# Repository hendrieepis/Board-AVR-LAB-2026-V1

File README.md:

# 📋 Panduan Desain: Shield Arduino Mega 2560 — PENS Expansion Board V2.0

---

## 📐 Spesifikasi Teknis

### 1. Dimensi & Form Factor

| Parameter | Nilai |
|---|---|
| Panjang | 101.6 mm / 4000 mil (exact Arduino Mega R3) |
| Lebar | 53.3 mm / 2098 mil (exact Arduino Mega R3) |
| Ketebalan PCB | 1.6 mm / 63 mil (FR4) |
| Lubang mounting | 4× (diameter 3.2 mm / 126 mil) |
| Jumlah layer | 2 (dua layer) |
| Konektor ke Mega | *Stackable female header* 2.54 mm / 100 mil |

### 2. Sumber Daya

- **Source:** Arduino Mega 5V rail saja (tidak ada *external power*)
- **Decoupling:** 4× 100 nF (0805) — distribusi dekat cluster MOSFET untuk menjaga stabilitas switching

### 3. Pin Assignment (WAJIB SAMA DENGAN WOKWI)

> ⚠️ **PENTING:** Pin *assignment* harus persis sama dengan simulator Wokwi PENS Elka. Jangan merubah *mapping* pin karena akan menyebabkan kode tidak kompatibel antara simulator dan *hardware* fisik.

#### 3.1. LED Array (8 LED Merah — PORTA)

| Arduino Pin | AVR Port | Device | Warna | Reference |
|---|---|---|---|---|
| D22 | PA0 | LED1 | Merah | D0 |
| D23 | PA1 | LED8 | Merah | D1 |
| D24 | PA2 | LED7 | Merah | D2 |
| D25 | PA3 | LED5 | Merah | D3 |
| D26 | PA4 | LED3 | Merah | D4 |
| D27 | PA5 | LED6 | Merah | D5 |
| D28 | PA6 | LED4 | Merah | D6 |
| D29 | PA7 | LED2 | Merah | D7 |

**Package:** LED SMD 0805 (`LED_SMD:LED_0805_2012Metric_Pad1.15x1.40mm_HandSolder`)

**Tata letak PCB:** Susun LED dalam satu baris dari PA0 di kiri hingga PA7 di kanan agar mahasiswa bisa membaca *pattern* `PORTA` secara visual.

#### 3.2. LED Indikator (2 LED)

| Arduino Pin | AVR Port | Device | Warna | Reference |
|---|---|---|---|---|
| D12 | PB6 | LED9 | Merah | DA1 |
| D13 | PB7 | LED10 | Hijau | DB1 |

**Package:** LED SMD 0805 (sama dengan LED array)

#### 3.3. Buzzer

| Arduino Pin | AVR Port | Device | Reference |
|---|---|---|---|
| D11 | PB5 | Buzzer (piezo/magnetic 5V) | BZ1 |

**Skema rangkaian:**

```
        +5V
         │
       ┌─┴─┐
     1 │ + │ BZ1
       │   │ Buzzer
     2 │   │
       └─┬─┘
         │
       ┌─┴─┐
       │R6 │ 1K
       └─┬─┘
         │ 3
   D11 1 ┤├─┐
    ●────┤  │ Q2
    │    ┤├─┘ BSS138
  ┌─┴─┐    │ 2
  │R5 │    │
  │1M │    │
  └─┬─┘    │
    │      │
   GND    GND
```

#### 3.4. Push Button (Active-LOW, 4 unit)

| Arduino Pin | AVR Port | Device | Reference |
|---|---|---|---|
| D10 | PB4 | BTN1 | SW1 |
| D9 | PH6 | BTN2 | SW2 |
| D8 | PH5 | BTN3 | SW3 |
| D7 | PH4 | BTN4 | SW4 |

**Skema rangkaian (debounce):**

```
   +5V
    │
  ┌─┴─┐
  │R13│ 10K
  └─┬─┘
    ●──── D7
  ┌─┴─┐
  │R14│ 1K
  └─┬─┘
    ●─────────┐
   o│         │
   SW4       ─┴─ C4
   SW_Push   ─┬─ 0.1uF
   o│         │
    ●─────────┘
    │
   GND
```

- **Package:** Tactile switch 6×6 mm THT (`Button_Switch_THT:SW_PUSH_6mm`)
- **Tinggi actuator:** Rekomendasi 7.3H (ergonomis untuk jari, tidak mudah rusak)
- Tombol aktif saat ditekan (menghubungkan pin ke GND)
- Menggunakan internal pull-up AVR (`INPUT_PULLUP` di kode) — tidak perlu resistor pull-up eksternal
- **Alasan pilih THT (bukan SMD):** Untuk praktikum mahasiswa, THT jauh lebih robust terhadap tekanan berulang dan perlakuan kasar. Jalur PCB tidak mudah rusak karena kaki pin masuk ke PTH (plated through-hole), bukan hanya solder di permukaan.

#### 3.5. Potensiometer & LDR (Input Analog)

| Arduino Pin | ADC Channel | Device | Reference | Tipe |
|---|---|---|---|---|
| A0 | ADC0 | POT1 | RV1 | Trimpot 10K |
| A1 | ADC1 | POT2 | RV2 | Trimpot 10K |
| A2 | ADC2 | LDR | R14 | GL5528 (5mm) |

**Package:**

- **Trimpot:** `Potentiometer_THT:Potentiometer_Bourns_3386P_Vertical` (Bourns 3386P 10K)
- **LDR:** `OptoDevice:R_LDR_5.1x4.3mm_P3.4mm_Vertical` (GL5528, pitch 3.4mm)

**Konfigurasi:**

- **Trimpot (RV1, RV2):** Voltage divider standar — Pin 1 ke +5V, Pin 3 ke GND, wiper (Pin 2) ke ADC
- **LDR (R14):** Voltage divider dengan resistor partner 10K (R_LDR ke +5V, R_10K ke GND, tap ke ADC)

---

## 🔌 Rangkaian Driver (MOSFET Isolation)

### Skema Driver LED (diulang untuk 8 LED PORTA + 2 LED indikator + Buzzer = 11 channel)

```
        +5V
         │
        ─┴─
        \ / D7
        ─┬─ LED
         │
       ┌─┴─┐
       │R32│ 1K
       └─┬─┘
         │ 3
  D29  1 ┤├─┐
   ●─────┤  │ Q12
   │     ┤├─┘ BSS138
 ┌─┴─┐     │ 2
 │R31│     │
 │1M │     │
 └─┬─┘     │
   │       │
  GND     GND
```

### Komponen per Channel LED

| # | Komponen | Nilai | Package | Fungsi |
|---|---|---|---|---|
| 1 | MOSFET | BSS138 | SOT-23 | Switch utama |
| 2 | Resistor pull-up | 10 kΩ | 0805 | Gate bias ke +5V |
| 3 | Resistor pull-down | 1 MΩ | 0805 | Cegah *flicker* saat pin INPUT |
| 4 | Resistor LED | 1 kΩ | 0805 | Pembatas arus LED (~3 mA) |
| 5 | LED | Merah/Hijau | 0805 | Indikator visual |

### Perilaku Driver

| Kondisi Pin Arduino | Gate MOSFET | LED |
|---|---|---|
| HIGH (5V) | HIGH | ON |
| LOW (0V) | LOW | OFF |
| INPUT (floating) | LOW (via R 1M) | OFF (tidak *flicker*) |

---

## 🔗 Antarmuka Komunikasi

### 1. Header I2C (JST PH 2.0, 4-pin)

**Reference:** J10 (atau salah satu dari J10, J11, J12)
**Footprint:** `Connector_JST:JST_PH_B4B-PH-K_1x04_P2.00mm_Vertical`

| Pin | Nama | Koneksi |
|---|---|---|
| 1 | GND | GND |
| 2 | VCC | +5V |
| 3 | SDA | Arduino pin 20 |
| 4 | SCL | Arduino pin 21 |

> **Catatan I2C pull-up:** ATmega2560 memiliki internal pull-up untuk SDA/SCL. Untuk modul I2C 5V standard (OLED, sensor), internal pull-up cukup. Jika menggunakan modul yang butuh pull-up eksternal, tambahkan resistor 4.7K di sisi modul.

### 2. Header SPI (JST PH 2.0, 6-pin)

**Reference:** J8 atau J9
**Footprint:** `Connector_JST:JST_PH_B6B-PH-K_1x06_P2.00mm_Vertical`

| Pin | Nama | Koneksi |
|---|---|---|
| 1 | GND | GND |
| 2 | VCC | +5V |
| 3 | MOSI | Arduino pin 51 |
| 4 | MISO | Arduino pin 50 |
| 5 | SCK | Arduino pin 52 |
| 6 | CS | Arduino pin 53 |

### 3. Header UART (JST PH 2.0, 4-pin)

**Reference:** J11 atau J12
**Footprint:** `Connector_JST:JST_PH_B4B-PH-K_1x04_P2.00mm_Vertical`

| Pin | Nama | Koneksi |
|---|---|---|
| 1 | GND | GND |
| 2 | VCC | +5V |
| 3 | TX1 | Arduino pin 18 (Serial1 TX) |
| 4 | RX1 | Arduino pin 19 (Serial1 RX) |

> Menggunakan **Serial1** (bukan Serial0) agar USB *debug* tetap tersedia untuk *Serial Monitor*.

**Praktik desain:**

- *Expose* semua pin yang digunakan di sisi atas dan bawah *board*
- *Silkscreen* dual label: "D22 / PA0", "A0 / ADC0", dst.
- Termasuk multiple *access point* untuk +5V dan GND

---

## 🎨 Prioritas Layout PCB

1. LED array disusun horizontal dari kiri ke kanan: PA0 → PA7
2. Push button dikelompokkan (4 tombol dalam satu baris)
3. Input analog dikelompokkan (2 trimpot + 1 LDR dalam satu area)
4. Connector JST di tepi *board* untuk akses kabel yang mudah
5. Silkscreen dual label (Arduino pin + AVR port) pada setiap pin *breakout*
6. Component reference (R1, C1, Q1, dll.) terlihat setelah *assembly*
7. **LDR penempatan:** Jauhkan minimal 20mm dari LED indikator untuk menghindari cross-talk cahaya

---

## 🏭 Spesifikasi PCB & Manufacturing

### Spesifikasi Fisik

| Parameter | Nilai |
|---|---|
| Layer | 2 |
| Material | FR4 1.6 mm |
| Copper weight | 1 oz (35 µm) |
| *Soldermask* | Hitam atau ungu |
| *Silkscreen* | Putih |
| Surface finish | HASL Lead-free (gratis) |
| *Ground plane* | *Bottom layer* |
| *Top layer* | Signal + komponen |

### Layer Strategy

```
TOP layer:    Body semua komponen (SMD & THT)
              SMD solder pads di sini
              Signal trace + VCC

BOTTOM layer: Solder pad untuk pin THT (saja)
              Ground plane solid
              Minimize signal trace
```

**Prinsip desain:**

- ❌ Bottom layer **JANGAN** dijadikan VCC plane
- ✅ Bottom layer = **Ground plane solid** (lebih baik untuk EMI, signal integrity, dan ADC accuracy)
- ✅ VCC sebagai **trace tebal** di top layer (0.5 mm / 20 mil)
- ✅ Decoupling capacitor (100 nF) dekat dengan cluster MOSFET
- ✅ Stitching via di area ground pour (1 via per 1–2 cm²) untuk low-impedance ground

### Bonus

**Bonus (optional, nilai plus):** Tambahkan **logo PENS** dan/atau **tulisan "Prodi Elka"** di area kosong **Bottom Silkscreen (B.Silkscreen)** sebagai identitas board. Bisa dalam bentuk:

- Logo PENS (import image ke KiCad)
- Tulisan "Prodi Elka - PENS" dengan KiCad text tool
- Atau kombinasi keduanya

Contoh:

```
┌────────────────────────────────────┐
│                                    │
│           [Logo PENS]              │
│                                    │
│        PENS EXPANSION BOARD        │
│           V2.0 (2026)              │
│      Prodi Teknik Elektronika      │
│                                    │
└────────────────────────────────────┘
```

---

## 📏 Design Rules untuk JLCPCB (Safe Settings)

> ⚠️ **PENTING:** Design rules di bawah ini adalah **recommended safe values** — lebih besar dari JLCPCB minimum — untuk margin terhadap manufacturing tolerance. Jangan mendesain persis di JLCPCB minimum karena risiko reject atau defect tinggi.

### Design Rules Cheatsheet

```
┌──────────────────────────────────────────────────────┐
│  PCB DESIGN RULES (JLCPCB Safe Settings)             │
├──────────────────────────────────────────────────────┤
│                                                      │
│  TRACK WIDTH:                                        │
│    Signal:  0.25 mm  (10 mil)                        │
│    Power:   0.5  mm  (20 mil)                        │
│                                                      │
│  CLEARANCE:                                          │
│    Track – track:  0.2 mm  (8 mil)                   │
│    Track – pad:    0.2 mm  (8 mil)                   │
│    Track – edge:   0.3 mm  (12 mil)                  │
│                                                      │
│  VIA:                                                │
│    Signal:  0.3 / 0.6 mm  (12 / 24 mil)              │
│    Power:   0.4 / 0.8 mm  (16 / 32 mil)              │
│                                                      │
│  HOLE (THT):                                         │
│    Min drill:     0.3 mm  (12 mil) – JLCPCB limit    │
│    Typical pin:   0.6 – 1.0 mm  (24 – 39 mil)        │
│    Annular ring:  0.15 mm  (6 mil) per side          │
│                                                      │
│  BOARD EDGE:                                         │
│    Copper – edge:     0.3 mm  (12 mil)               │
│    Component – edge:  1.0 mm  (39 mil)               │
│    Mounting – edge:   2.0 mm  (79 mil)               │
│                                                      │
│  SILKSCREEN:                                         │
│    Line width:   0.15 mm  (6 mil)                    │
│    Text height:  1.0 mm  (39 mil)                    │
│    Pad clear:    0.15 mm  (6 mil)                    │
│                                                      │
│  UNIT CONVERSION:                                    │
│    1 mil = 0.0254 mm                                 │
│    1 mm  = 39.37 mil                                 │
│                                                      │
└──────────────────────────────────────────────────────┘
```

> 💡 **Tip praktis:** Biasakan mikir dalam mil untuk track width dan mm untuk board dimension — convention yang umum di komunitas PCB global. KiCad support keduanya, switch via View → Units atau shortcut Ctrl+U.

**Current capacity:** Trace 0.5 mm (20 mil) pada 1 oz copper = ~1.6 A (10°C rise). Estimasi beban project ini ≈ 300 mA (10 LED × 3 mA + buzzer 50 mA + modul external 200 mA), jadi margin ~5× — sangat aman.

### Clearance Komponen

**Clearance** = jarak minimum antara dua komponen di PCB, diukur dari body/pad komponen satu ke body/pad komponen sebelahnya.

```
[Komponen A] ←─── clearance ───→ [Komponen B]
   body                              body
```

| Antar Komponen | Recommended | Alasan |
|---|---|---|
| SMD 0805 – SMD 0805 | **0.5 mm (20 mil)** | Akses solder iron |
| BSS138 (SOT-23) – neighbor | **1.0 mm (39 mil)** | Akses untuk rework |
| LED 0805 – LED 0805 (array PORTA) | **1.0 mm (39 mil)** | Visual separation, tidak overlap cahaya |
| Tactile switch (THT) – neighbor | **3 mm (118 mil)** | Space untuk jari menekan |
| Trimpot 3386P – neighbor | **2 mm (79 mil)** | Akses obeng untuk adjust |
| **LDR – LED indikator** | **20–30 mm (787–1181 mil)** | Hindari cross-talk cahaya ke LDR |
| JST PH – tepi PCB | **5 mm (197 mil)** | Clearance kabel saat dicolok |

> Ini berbeda dengan trace clearance (jarak antar jalur tembaga). Clearance komponen lebih ke urusan fisik/mekanis, sedangkan trace clearance urusan elektris.

### Cara Set di KiCad

1. PCB Editor → **File → Board Setup**
2. Tab **Design Rules → Constraints** → input nilai Global Constraints
3. Tab **Design Rules → Net Classes** → tambahkan class "Power", assign net VCC dan GND
4. Save

**Verifikasi sebelum export:** Inspect → **Design Rules Checker (DRC)** → target **zero error**, warning silkscreen diperiksa manual.

---

## ✅ Checklist Sebelum Submit Gerber

### Phase 1: KiCad DRC

- [ ] DRC run dengan zero error
- [ ] Warning silkscreen sudah direview (silkscreen overlap pad akan auto-remove oleh JLCPCB)
- [ ] Tidak ada unconnected net

### Phase 2: Visual Review

- [ ] **3D View** (Alt+3) — semua komponen muncul & positioned benar
- [ ] **Ground plane** di bottom layer solid, tidak split oleh signal
- [ ] **Stitching via** di ground pour, kerapatan 1 per 1–2 cm²
- [ ] **Decoupling cap** (100 nF) dekat dengan cluster MOSFET
- [ ] **Silkscreen** label Arduino pin + AVR port readable
- [ ] **Reference designator** (R1, Q1, dll.) visible setelah assembly

### Phase 3: Mechanical Fit

- [ ] **Board outline** (Edge.Cuts) closed polygon, 101.6 × 53.3 mm
- [ ] **4 mounting hole** di lokasi exact Arduino Mega R3
- [ ] **Stackable pin header** align dengan Arduino Mega socket
- [ ] **Clearance barrel jack** + **USB connector** Mega
- [ ] Tinggi komponen < 15 mm (agar shield bisa di-stack)

### Phase 4: Print 1:1 Test

- [ ] Print PDF top + bottom layer 1:1 di kertas
- [ ] Verifikasi skala dengan penggaris
- [ ] Taruh komponen fisik di atas print
- [ ] Footprint match pad, orientasi benar
- [ ] Komponen THT tidak bentrok dengan komponen SMD sekitar

### Phase 5: Gerber Export & Review

- [ ] File → **Fabrication Outputs → Gerbers** → export semua layer
- [ ] **Generate drill files** (.drl) — centang!
- [ ] Upload zip ke **JLCPCB Gerber Viewer** (online)
- [ ] Visual inspection setiap layer (top copper, bottom copper, silkscreen, drill)
- [ ] Verifikasi board size di viewer

### Common Rejection Reasons dari JLCPCB

| Masalah | Solusi |
|---|---|
| Trace terlalu kecil (<6 mil) | Set min track width 0.2 mm (8 mil) |
| Hole <0.3 mm (12 mil) | Min drill 0.3 mm (12 mil) untuk via, 0.6 mm (24 mil) untuk pin THT |
| Trace terlalu dekat ke tepi PCB | Edge clearance minimum 0.3 mm (12 mil) — safer 0.5 mm (20 mil) |
| Silkscreen overlap pad | Kasih gap 0.15 mm (6 mil) (atau ikhlaskan auto-remove) |
| Missing drill file | Export .drl terpisah saat Gerber export |
| Board outline tidak closed | Edge.Cuts harus single closed polygon |

---

## 💪 Pro Tips dari Pengalaman Fabrikasi

### 1. Mulai DRC Lenient, Tighten Later

Saat awal routing, set DRC minimum (0.127 mm) biar KiCad router fleksibel. Setelah semua trace selesai, **tighten DRC** ke nilai recommended (0.2 mm) lalu re-run DRC. Fix error yang muncul satu per satu.

### 2. Jangan Mepet Manufacturing Minimum

JLCPCB minimum 0.127 mm, tapi desain di 0.2 mm. Manufacturing punya tolerance ±0.05 mm, kalau mepet minimum → kena tolerance minus → fail. Selalu kasih margin.

### 3. Test Points untuk Debugging

Tambahkan **test points** (pad TH 1 mm diameter) di signal kritikal untuk kemudahan debugging pasca-assembly:

| Signal | Lokasi Recommended |
|---|---|
| VCC 5V | Dekat power input header |
| GND | Multiple (minimum 3 lokasi di PCB) |
| Analog A0–A2 | Dekat trimpot/LDR |
| UART TX/RX | Dekat JST PH UART |
| SPI bus | Dekat JST PH SPI |
| Gate MOSFET | 1–2 channel sebagai sample (untuk scope) |

**Footprint:** `TestPoint:TestPoint_Pad_D1.5mm` atau `TestPoint_THTPad_1.0x1.0mm_Drill0.5mm`

### 4. Print 1:1 Manual Check

Sebelum klik "Submit" di JLCPCB:

1. Export PDF top + bottom layer dengan scale **1:1**
2. Print di kertas, verifikasi skala dengan penggaris (pastikan PCB 101.6 mm sesuai penggaris)
3. Taruh komponen fisik di atas cetakan
4. Cek alignment footprint, clearance, orientasi
5. Simulasi: tekan tombol, putar trimpot, colok JST — apakah ada yang bentrok?

**10 menit manual check = save $10 wasted PCB + 2 minggu waiting.**

### 5. Save Gerber sebagai "Release"

Setelah submit, **tag Gerber file** dengan versi (misal `ExpansionBoard-V1.0-Gerber.zip`) dan commit ke Git. Kalau nanti ada revisi, bisa compare version history.

---

## 📚 Referensi & Resources

### Datasheet Komponen Kritis

- BSS138 MOSFET Datasheet
- ATmega2560 (Arduino Mega) Datasheet
- JST PH Series Datasheet
- Bourns 3386P Potentiometer Datasheet
- LDR GL5528 Datasheet

### Tutorial & Learning

- KiCad Getting Started
- JLCPCB Ordering Guide

### Inspirasi Desain

- Cytron Maker Pi Pico Schematic — referensi MOSFET isolation topology
- Arduino Mega R3 Schematic

### Library KiCad

- SnapEDA Arduino Mega 2560 Rev3

## Release

VersiA

- KICAD ->    [versiA](versiA) 

- Gerver->  https://github.com/hendrieepis/Board-AVR-LAB-2026-V1/blob/master/versiA/gerber.zip

VersiB

- KICAD ->     [VersiB](VersiB) 

- Gerber ->   https://github.com/hendrieepis/Board-AVR-LAB-2026-V1/blob/master/VersiB/gerber.zip

Pcloud

- https://e.pcloud.link/publink/show?code=kZzxKcZidlPBQnEcohYrJGMhkQTauFlQ4nX

## Test hardware

-  [test-hardware](test-hardware)

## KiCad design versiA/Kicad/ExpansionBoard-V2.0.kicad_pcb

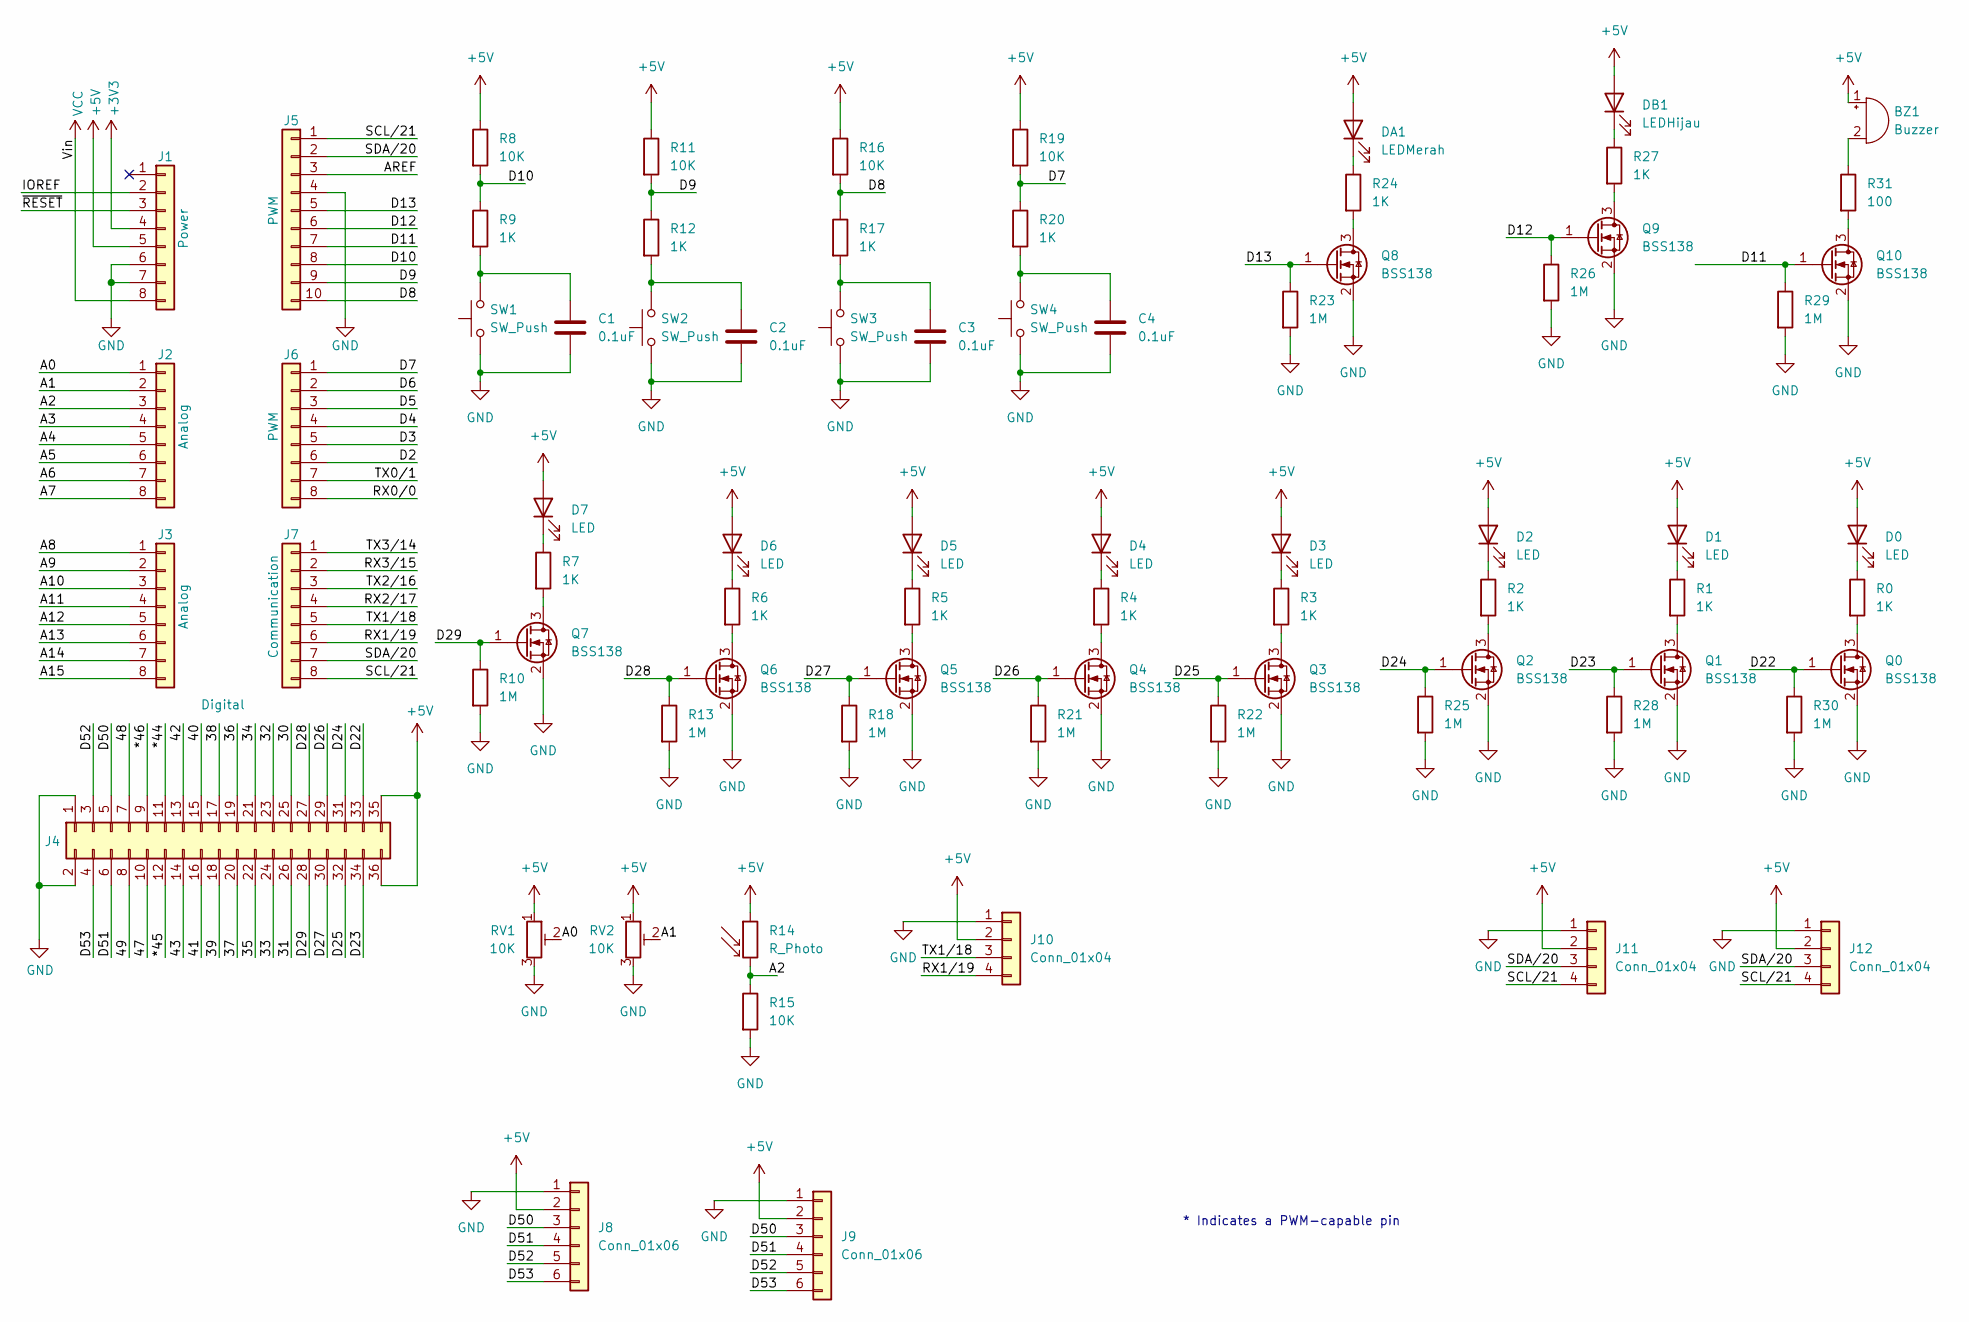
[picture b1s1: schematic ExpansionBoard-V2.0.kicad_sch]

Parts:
BZ1: Buzzer; Buzzer_TDK_PS1240P02BT_D12.2mm_H6.5mm
C1, C2, C3, C4: 0.1uF; C_0805_2012Metric_Pad1.18x1.45mm_HandSolder
D0, D1, D2, D3, D4, D5, D6, D7: LED; LED_0805_2012Metric_Pad1.15x1.40mm_HandSolder
DA1: LEDMerah; LED_0805_2012Metric_Pad1.15x1.40mm_HandSolder
DB1: LEDHijau; LED_0805_2012Metric_Pad1.15x1.40mm_HandSolder
J1: Power; PinSocket_1x08_P2.54mm_Vertical
J2, J3: Analog; PinSocket_1x08_P2.54mm_Vertical
J4: Digital; PinSocket_2x18_P2.54mm_Vertical
J5: PWM; PinSocket_1x10_P2.54mm_Vertical
J6: PWM; PinSocket_1x08_P2.54mm_Vertical
J7: Communication; PinSocket_1x08_P2.54mm_Vertical
J8, J9: Conn_01x06; JST_PH_B6B-PH-K_1x06_P2.00mm_Vertical
J10, J11, J12: Conn_01x04; JST_PH_B4B-PH-K_1x04_P2.00mm_Vertical
Q0, Q1, Q2, Q3, Q4, Q5, Q6, Q7, Q8, Q9, Q10: BSS138; SOT-23_Handsoldering
R0, R1, R2, R3, R4, R5, R6, R7, R9, R12, R17, R20, R24, R27: 1K; R_0805_2012Metric_Pad1.20x1.40mm_HandSolder
R8, R11, R15, R16, R19: 10K; R_0805_2012Metric_Pad1.20x1.40mm_HandSolder
R10, R13, R18, R21, R22, R23, R25, R26, R28, R29, R30: 1M; R_0805_2012Metric_Pad1.20x1.40mm_HandSolder
R14: R_Photo; R_LDR_5.1x4.3mm_P3.4mm_Vertical
R31: 100; R_0805_2012Metric_Pad1.20x1.40mm_HandSolder
RV1, RV2: 10K; Potentiometer_Bourns_3386P_Vertical
SW1, SW2, SW3, SW4: SW_Push; SW_PUSH_6mm

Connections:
+3V3: J1.4
+5V: BZ1.1 (+), D0.2 (A), D1.2 (A), D2.2 (A), D3.2 (A), D4.2 (A), D5.2 (A), D6.2 (A), D7.2 (A), DA1.2 (A), DB1.2 (A), J1.5, J4.35, J4.36, J8.2, J9.2, J10.2, J11.2, J12.2, R8.1, R11.1, R14.1, R16.1, R19.1, RV1.1, RV2.1
/30: J4.25
/31: J4.26
/32: J4.23
/33: J4.24
/34: J4.21
/35: J4.22
/36: J4.19
/37: J4.20
/38: J4.17
/39: J4.18
/40: J4.15
/41: J4.16
/42: J4.13
/43: J4.14
/47: J4.10
/48: J4.7
/49: J4.8
/*44: J4.11
/*45: J4.12
/*46: J4.9
/A0: J2.1, RV1.2
/A1: J2.2, RV2.2
/A2: J2.3, R14.2, R15.1
/A3: J2.4
/A4: J2.5
/A5: J2.6
/A6: J2.7
/A7: J2.8
/A8: J3.1
/A9: J3.2
/A10: J3.3
/A11: J3.4
/A12: J3.5
/A13: J3.6
/A14: J3.7
/A15: J3.8
/AREF: J5.3
/D2: J6.6
/D3: J6.5
/D4: J6.4
/D5: J6.3
/D6: J6.2
/D7: J6.1, R19.2, R20.1
/D8: J5.10, R16.2, R17.1
/D9: J5.9, R11.2, R12.1
/D10: J5.8, R8.2, R9.1
/D11: J5.7, Q10.1 (G), R29.1
/D12: J5.6, Q9.1 (G), R26.1
/D13: J5.5, Q8.1 (G), R23.1
/D22: J4.33, Q0.1 (G), R30.1
/D23: J4.34, Q1.1 (G), R28.1
/D24: J4.31, Q2.1 (G), R25.1
/D25: J4.32, Q3.1 (G), R22.1
/D26: J4.29, Q4.1 (G), R21.1
/D27: J4.30, Q5.1 (G), R18.1
/D28: J4.27, Q6.1 (G), R13.1
/D29: J4.28, Q7.1 (G), R10.1
/D50: J4.5, J8.3, J9.3
/D51: J4.6, J8.4, J9.4
/D52: J4.3, J8.5, J9.5
/D53: J4.4, J8.6, J9.6
/IOREF: J1.2
/RX0/0: J6.8
/RX1/19: J7.6, J10.4
/RX2/17: J7.4
/RX3/15: J7.2
/SCL/21: J5.1, J7.8, J11.4, J12.4
/SDA/20: J5.2, J7.7, J11.3, J12.3
/TX0/1: J6.7
/TX1/18: J7.5, J10.3
/TX2/16: J7.3
/TX3/14: J7.1
/~RESET: J1.3
GND: C1.2, C2.2, C3.2, C4.2, J1.6, J1.7, J4.1, J4.2, J5.4, J8.1, J9.1, J10.1, J11.1, J12.1, Q0.2 (S), Q1.2 (S), Q2.2 (S), Q3.2 (S), Q4.2 (S), Q5.2 (S), Q6.2 (S), Q7.2 (S), Q8.2 (S), Q9.2 (S), Q10.2 (S), R10.2, R13.2, R15.2, R18.2, R21.2, R22.2, R23.2, R25.2, R26.2, R28.2, R29.2, R30.2, RV1.3, RV2.3, SW1.1, SW2.1, SW3.1, SW4.1
unnamed: BZ1.2 (-), R31.1
unnamed: C1.1, R9.2, SW1.2
unnamed: C2.1, R12.2, SW2.2
unnamed: C3.1, R17.2, SW3.2
unnamed: C4.1, R20.2, SW4.2
unnamed: D0.1 (K), R0.1
unnamed: D1.1 (K), R1.1
unnamed: D2.1 (K), R2.1
unnamed: D3.1 (K), R3.1
unnamed: D4.1 (K), R4.1
unnamed: D5.1 (K), R5.1
unnamed: D6.1 (K), R6.1
unnamed: D7.1 (K), R7.1
unnamed: DA1.1 (K), R24.1
unnamed: DB1.1 (K), R27.1
unnamed: Q0.3 (D), R0.2
unnamed: Q1.3 (D), R1.2
unnamed: Q2.3 (D), R2.2
unnamed: Q3.3 (D), R3.2
unnamed: Q4.3 (D), R4.2
unnamed: Q5.3 (D), R5.2
unnamed: Q6.3 (D), R6.2
unnamed: Q7.3 (D), R7.2
unnamed: Q8.3 (D), R24.2
unnamed: Q9.3 (D), R27.2
unnamed: Q10.3 (D), R31.2
VCC: J1.8

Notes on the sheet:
* Indicates a PWM-capable pin

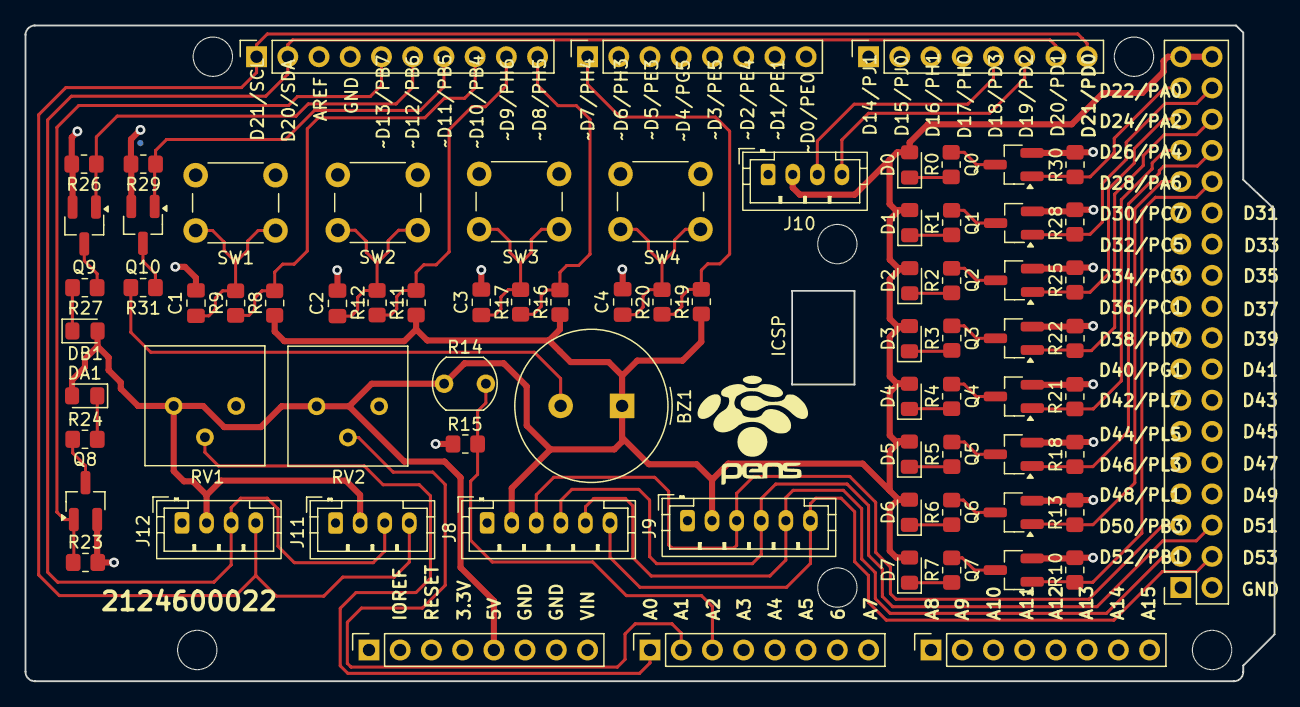
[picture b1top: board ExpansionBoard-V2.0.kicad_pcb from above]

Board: 2 copper layers, 101.6 x 53.3 mm, 82 parts (0 on the bottom side), 54 nets.

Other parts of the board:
MH1, MH2, MH3, MH4, MH5, MH6: MountingHole_3.2mm
